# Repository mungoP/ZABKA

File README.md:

# ŻABKA

**Zero-moment Assisted Bipedal Kinetic Android**

By Mungo Prus-Shearer and Adam Chrostowski

ŻABKA ("little frog" in Polish) is a DIY 3D-printed bipedal robot with custom FOC motor controllers on every joint. The current focus is the legs.

<p align="center"><em>Left: leg assembly (Onshape). Right: motor controller board (KiCad).</em></p>

## Specs (planned)

|                      |                                                                                                |
| -------------------- | ---------------------------------------------------------------------------------------------- |
| **Height**           | 0.45m (without upper body) 0.85m (full body)                                                   |
| **Legs**             | 5 DoF each (3 hip, 1 knee, 1 ankle), 10 DoF total                                              |
| **Actuators**        | MAD 5008 170KV BLDC motors, each with a custom STSPIN32G4 FOC controller board, on one CAN bus |
| **Compute**          | Raspberry Pi 4 running the walking policy, ESP32-C3 as the real-time CAN bridge                |
| **Power**            | 12S LiPo, two 6S 4000 mAh packs soldered in series (36–50.4 V)                                 |
| **Structure**        | 3D-printed PETG, 4 walls, 10–20 % infill                                                       |
| **Estimated weight** | ~8 kg without arms                                                                             |

## System overview

```mermaid
flowchart LR
    PI["Raspberry Pi 4<br/>RL policy"] <-- "USB serial" --> ESP["ESP32-C3<br/>CAN bridge"]
    IMU["IMU"] --> ESP
    ESP <-- "CAN 1 Mbps" --> J["10 × motor + FOC board<br/>(5 per leg)"]
    BAT["12S LiPo + BMS"] -- "36–50.4 V" --> J
    BAT -- "5 V buck" --> PI
```

The Pi runs the walking policy at 50 Hz. The ESP32 exchanges commands and joint state with all 10 motor boards over CAN at 200 Hz, and each board closes its own FOC current loop and PD position loop. See [`docs/system_architecture.md`](docs/system_architecture.md) for the full design.

## Repository map

| Path                     | Contents                                                                  |
| ------------------------ | ------------------------------------------------------------------------- |
| [`BOM.csv`](BOM.csv)     | Combined bill of materials with running total                             |
| [`docs/`](docs/)         | System architecture, CAN protocol, per-category BOMs, datasheets          |
| [`cad/`](cad/)           | Onshape link and STEP exports of the printed parts                        |
| [`pcb/`](pcb/)           | KiCad project and JLCPCB fabrication files for the motor controller board |
| [`lib/`](lib/)           | Custom KiCad symbols, footprints and 3D models                            |
| [`firmware/`](firmware/) | Motor board FOC firmware and ESP32 CAN bridge firmware                    |
| [`software/`](software/) | Simulation, policy training and the code that runs on the Pi              |

## Status

| Subsystem                     | Status                                                                   |
| ----------------------------- | ------------------------------------------------------------------------ |
| Mechanical design             | Done ([Onshape](cad/))                                                   |
| 3D printing                   | In progress                                                              |
| Motor controller board        | Ordered from JLCPCB, shipping                                            |
| Motors, bearings, fasteners   | In hand                                                                  |
| Control and power electronics | Being purchased ([`electronics_BOM.csv`](docs/BOMs/electronics_BOM.csv)) |
| Firmware                      | Planned                                                                  |
| Walking policy                | Planned                                                                  |

## License

ŻABKA is open source:

- **Hardware** (`pcb/`, `lib/`, `cad/`): [CERN-OHL-S-2.0](LICENSES/CERN-OHL-S-2.0.txt)
- **Firmware and software** (`firmware/`, `software/`): [GPL-3.0-or-later](LICENSES/GPL-3.0.txt)
- **Documentation** (`docs/`, READMEs, BOMs): [CC BY-SA 4.0](LICENSES/CC-BY-SA-4.0.txt)

Anyone may use, modify, build and sell the designs, as long as modified versions are released under the same licence. See [`LICENSE`](LICENSE) for details.

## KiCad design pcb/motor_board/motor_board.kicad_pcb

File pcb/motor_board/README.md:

# Motor Board Planned Components

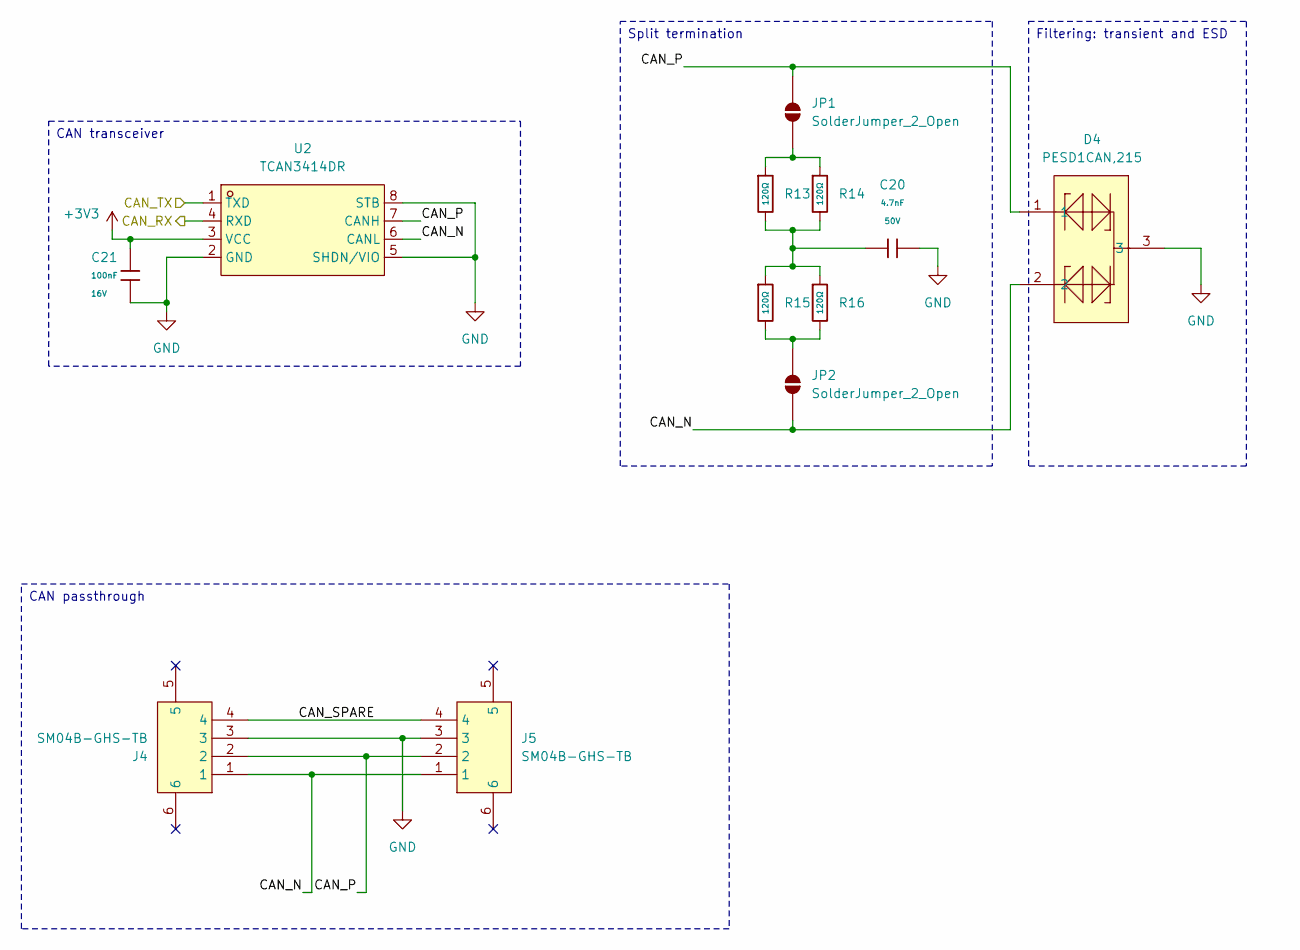
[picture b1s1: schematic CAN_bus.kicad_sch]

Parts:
C20: 4.7nF; C_0402; Voltage Rated 50V; Tolerance ±10%; Part 0402B472K500NT; LCSC C1538
C21: 100nF; C_0402; Voltage Rated 16V; Tolerance ±10%; Part CL05B104KO5NNNC; LCSC C1525
D4: PESD1CAN,215; SOT-23_L2.9-W1.3-P1.90-LS2.4-BR; MPN PESD1CAN,215; LCSC Part C15771
J4, J5: SM04B-GHS-TB; CONN-SMD_4P-P1.25_SM04B-GHS-TB-LF-SN; MPN SM04B-GHS-TB(LF)(SN); LCSC Part C189895
JP1, JP2: SolderJumper_2_Open; SolderJumper-2_P1.3mm_Open_Pad1.0x1.5mm
R13, R14, R15, R16: 120Ω; R_0402; Overload Voltage (Max) 50V; Tolerance ±1%; Part 0402WGF1200TCE; LCSC C25079
U2: TCAN3414DR; SOIC-8_L4.9-W3.9-P1.27-LS6.0-BL; MPN TCAN3414DR; LCSC Part C22396693

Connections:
+3V3: C21.1, U2.3 (VCC); also elsewhere on the board
/CAN bus/CAN_N: D4.2, J4.1, J5.1, JP2.1 (A), U2.6 (CANL)
/CAN bus/CAN_P: D4.1, J4.2, J5.2, JP1.2 (B), U2.7 (CANH)
/CAN bus/CAN_RX: U2.4 (RXD); also elsewhere on the board
/CAN bus/CAN_SPARE: J4.4, J5.4
/CAN bus/CAN_TX: U2.1 (TXD); also elsewhere on the board
GND: C20.2, C21.2, D4.3, J4.3, J5.3, U2.2 (GND), U2.5 (SHDN/VIO), U2.8 (STB); also elsewhere on the board
unnamed: C20.1, R13.2, R14.2, R15.1, R16.1
unnamed: JP1.1 (A), R13.1, R14.1
unnamed: JP2.2 (B), R15.2, R16.2

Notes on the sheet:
Split termination
CAN transceiver
CAN passthrough
Filtering: transient and ESD

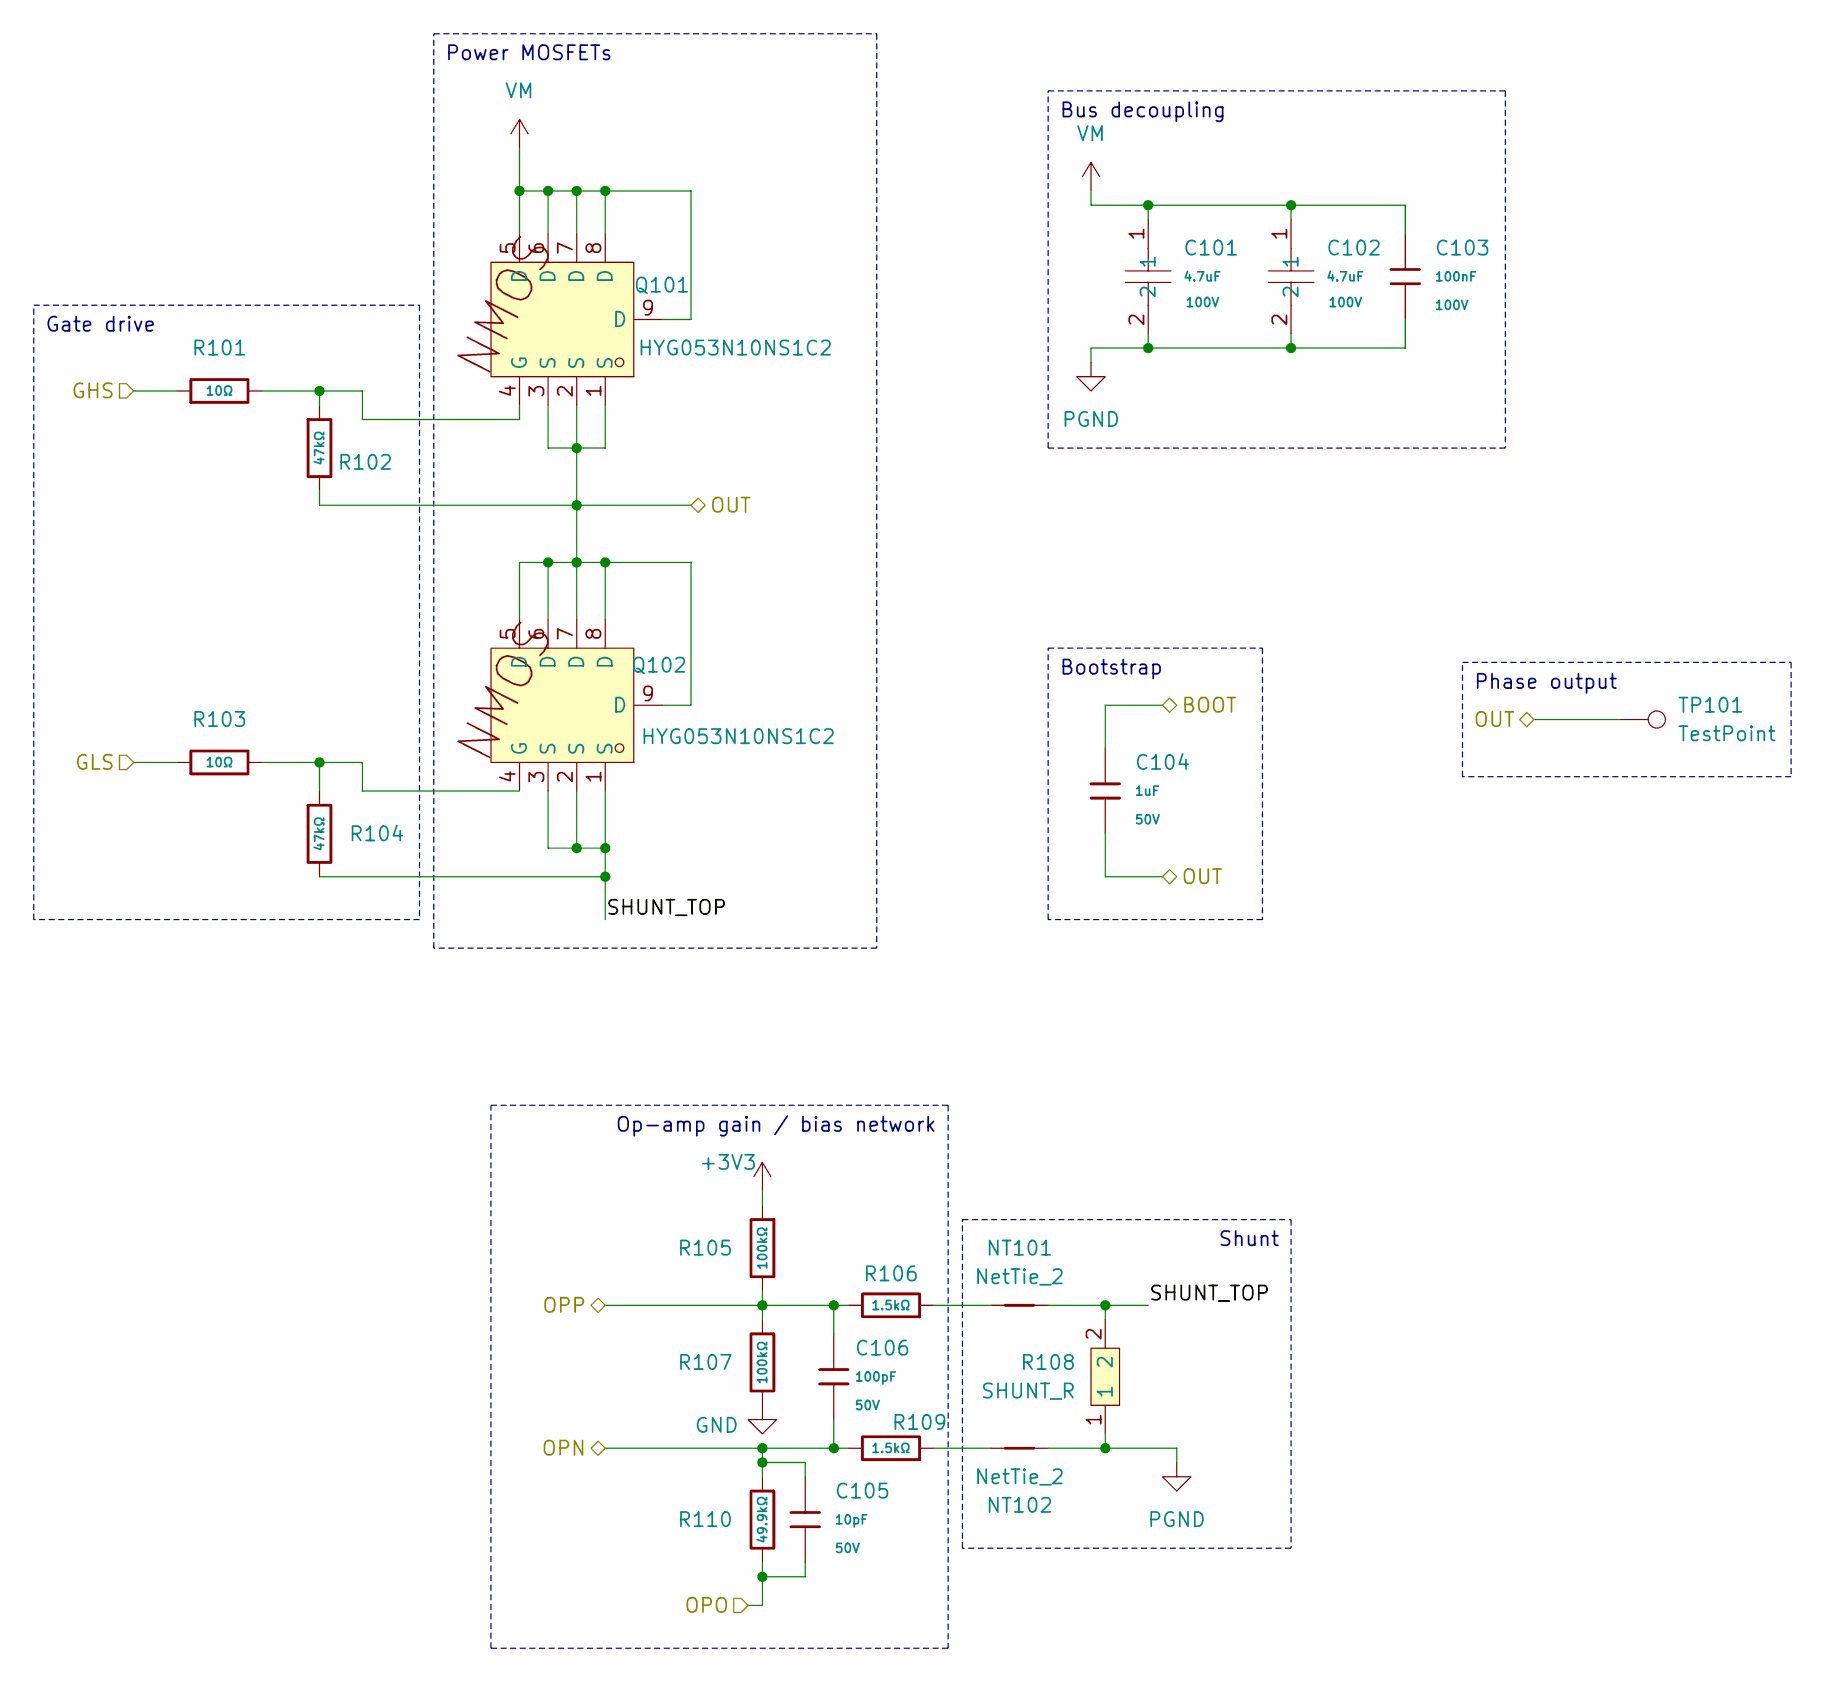
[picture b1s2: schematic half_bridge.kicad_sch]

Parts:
C101, C102: 4.7uF; C1210_no-silk; MPN C1210X475K101T; LCSC Part C337978
C103: 100nF; C_0805; Voltage Rated 100V; Tolerance ±10%; Part CL21B104KCFNNNE; LCSC C28233
C104: 1uF; C_0603; Voltage Rated 50V; Tolerance ±10%; Part CL10A105KB8NNNC; LCSC C15849
C105: 10pF; C_0402; Voltage Rated 50V; Tolerance ±5%; Part CL05C100JB5NNNC; LCSC C32949
C106: 100pF; C_0402; Voltage Rated 50V; Tolerance ±5%; Part 0402CG101J500NT; LCSC C1546
NT101, NT102: NetTie_2; NetTie-2_SMD_Pad0.5mm
Q101, Q102: HYG053N10NS1C2; PDFN-8_L5.8-W5.0-P1.27-LS6.2-BL; MPN HYG053N10NS1C2; LCSC Part C2986239
R101, R103: 10Ω; R_0402; Overload Voltage (Max) 50V; Tolerance ±1%; Part 0402WGF100JTCE; LCSC C25077
R102, R104: 47kΩ; R_0402; Overload Voltage (Max) 50V; Tolerance ±1%; Part 0402WGF4702TCE; LCSC C25792
R105, R107: 100kΩ; R_0603; Overload Voltage (Max) 75V; Tolerance ±1%; Part 0603WAF1003T5E; LCSC C25803
R106, R109: 1.5kΩ; R_0603; Overload Voltage (Max) 75V; Tolerance ±1%; Part 0603WAF1501T5E; LCSC C22843
R108: SHUNT_R; RES-SMD_L6.4-W3.2_LR2512D-3W-1MR; MPN LR2512D-3W-1mR-1%; LCSC Part C500734
R110: 49.9kΩ; R_0402; Overload Voltage (Max) 50V; Tolerance ±1%; Part 0402WGF4992TCE; LCSC C25897
TP101: TestPoint; TestPoint_Pad_4.0x4.0mm

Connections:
+3V3: R105.1; also elsewhere on the board
/Controller/BOOT1: C104.1; also elsewhere on the board
/Controller/GHS1: R101.1; also elsewhere on the board
/Controller/GLS1: R103.1; also elsewhere on the board
/Controller/OPN1: C105.1, C106.2, R109.2, R110.1; also elsewhere on the board
/Controller/OPO1: C105.2, R110.2; also elsewhere on the board
/Controller/OPP1: C106.1, R105.2, R106.2, R107.1; also elsewhere on the board
/Controller/OUT1: C104.2, Q101.1 (S), Q101.2 (S), Q101.3 (S), Q102.5 (D), Q102.6 (D), Q102.7 (D), Q102.8 (D), Q102.9 (D), R102.2, TP101.1 (1_1); also elsewhere on the board
/Half bridge - U/SHUNT_TOP: NT101.1, Q102.1 (S), Q102.2 (S), Q102.3 (S), R104.2, R108.2
GND: R107.2; also elsewhere on the board
unnamed: NT101.2, R106.1
unnamed: NT102.1, R109.1
unnamed: Q101.4 (G), R101.2, R102.1
unnamed: Q102.4 (G), R103.2, R104.1
PGND: C101.2, C102.2, C103.2, NT102.2, R108.1; also elsewhere on the board
VM: C101.1, C102.1, C103.1, Q101.5 (D), Q101.6 (D), Q101.7 (D), Q101.8 (D), Q101.9 (D); also elsewhere on the board

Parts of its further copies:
C201, C202, C301, C302: 4.7uF; C1210_no-silk; MPN C1210X475K101T; LCSC Part C337978
C203, C303: 100nF; C_0805; Voltage Rated 100V; Tolerance ±10%; Part CL21B104KCFNNNE; LCSC C28233
C204, C304: 1uF; C_0603; Voltage Rated 50V; Tolerance ±10%; Part CL10A105KB8NNNC; LCSC C15849
C205, C305: 10pF; C_0402; Voltage Rated 50V; Tolerance ±5%; Part CL05C100JB5NNNC; LCSC C32949
C206, C306: 100pF; C_0402; Voltage Rated 50V; Tolerance ±5%; Part 0402CG101J500NT; LCSC C1546
NT201, NT202, NT301, NT302: NetTie_2; NetTie-2_SMD_Pad0.5mm
Q201, Q202, Q301, Q302: HYG053N10NS1C2; PDFN-8_L5.8-W5.0-P1.27-LS6.2-BL; MPN HYG053N10NS1C2; LCSC Part C2986239
R201, R203, R301, R303: 10Ω; R_0402; Overload Voltage (Max) 50V; Tolerance ±1%; Part 0402WGF100JTCE; LCSC C25077
R202, R204, R302, R304: 47kΩ; R_0402; Overload Voltage (Max) 50V; Tolerance ±1%; Part 0402WGF4702TCE; LCSC C25792
R205, R207, R305, R307: 100kΩ; R_0603; Overload Voltage (Max) 75V; Tolerance ±1%; Part 0603WAF1003T5E; LCSC C25803
R206, R209, R306, R309: 1.5kΩ; R_0603; Overload Voltage (Max) 75V; Tolerance ±1%; Part 0603WAF1501T5E; LCSC C22843
R208, R308: SHUNT_R; RES-SMD_L6.4-W3.2_LR2512D-3W-1MR; MPN LR2512D-3W-1mR-1%; LCSC Part C500734
R210, R310: 49.9kΩ; R_0402; Overload Voltage (Max) 50V; Tolerance ±1%; Part 0402WGF4992TCE; LCSC C25897
TP201, TP301: TestPoint; TestPoint_Pad_4.0x4.0mm

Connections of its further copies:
+3V3: R205.1, R305.1; also elsewhere on the board
/Controller/BOOT2: C204.1; also elsewhere on the board
/Controller/BOOT3: C304.1; also elsewhere on the board
/Controller/GHS2: R201.1; also elsewhere on the board
/Controller/GHS3: R301.1; also elsewhere on the board
/Controller/GLS2: R203.1; also elsewhere on the board
/Controller/GLS3: R303.1; also elsewhere on the board
/Controller/OPN2: C205.1, C206.2, R209.2, R210.1; also elsewhere on the board
/Controller/OPN3: C305.1, C306.2, R309.2, R310.1; also elsewhere on the board
/Controller/OPO2: C205.2, R210.2; also elsewhere on the board
/Controller/OPO3: C305.2, R310.2; also elsewhere on the board
/Controller/OPP2: C206.1, R205.2, R206.2, R207.1; also elsewhere on the board
/Controller/OPP3: C306.1, R305.2, R306.2, R307.1; also elsewhere on the board
/Controller/OUT2: C204.2, Q201.1 (S), Q201.2 (S), Q201.3 (S), Q202.5 (D), Q202.6 (D), Q202.7 (D), Q202.8 (D), Q202.9 (D), R202.2, TP201.1 (1_1); also elsewhere on the board
/Controller/OUT3: C304.2, Q301.1 (S), Q301.2 (S), Q301.3 (S), Q302.5 (D), Q302.6 (D), Q302.7 (D), Q302.8 (D), Q302.9 (D), R302.2, TP301.1 (1_1); also elsewhere on the board
/Half bridge - V/SHUNT_TOP: NT201.1, Q202.1 (S), Q202.2 (S), Q202.3 (S), R204.2, R208.2
/Half bridge - W/SHUNT_TOP: NT301.1, Q302.1 (S), Q302.2 (S), Q302.3 (S), R304.2, R308.2
GND: R207.2, R307.2; also elsewhere on the board
unnamed: NT201.2, R206.1
unnamed: NT202.1, R209.1
unnamed: NT301.2, R306.1
unnamed: NT302.1, R309.1
unnamed: Q201.4 (G), R201.2, R202.1
unnamed: Q202.4 (G), R203.2, R204.1
unnamed: Q301.4 (G), R301.2, R302.1
unnamed: Q302.4 (G), R303.2, R304.1
PGND: C201.2, C202.2, C203.2, C301.2, C302.2, C303.2, NT202.2, NT302.2, R208.1, R308.1; also elsewhere on the board
VM: C201.1, C202.1, C203.1, C301.1, C302.1, C303.1, Q201.5 (D), Q201.6 (D), Q201.7 (D), Q201.8 (D), Q201.9 (D), Q301.5 (D), Q301.6 (D), Q301.7 (D), Q301.8 (D), Q301.9 (D); also elsewhere on the board

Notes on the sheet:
Bootstrap
Gate drive
Shunt
Bus decoupling
Power MOSFETs
Op-amp gain / bias network
Phase output

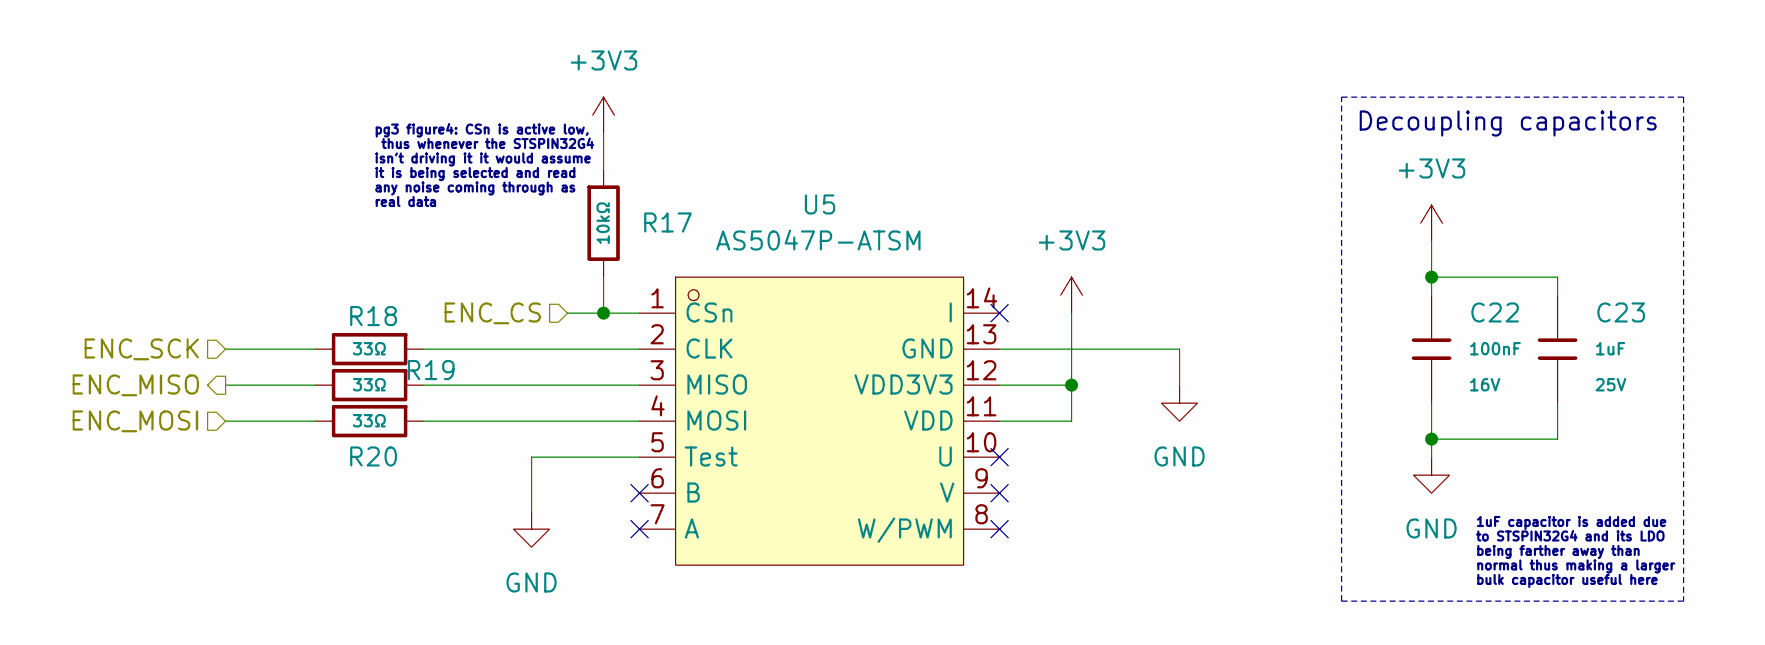
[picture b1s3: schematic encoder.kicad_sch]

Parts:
C22: 100nF; C_0402; Voltage Rated 16V; Tolerance ±10%; Part CL05B104KO5NNNC; LCSC C1525
C23: 1uF; C_0402; Voltage Rated 25V; Tolerance ±10%; Part CL05A105KA5NQNC; LCSC C52923
R17: 10kΩ; R_0402; Overload Voltage (Max) 50V; Tolerance ±1%; Part 0402WGF1002TCE; LCSC C25744
R18, R19, R20: 33Ω; R_0402; Overload Voltage (Max) 50V; Tolerance ±1%; Part 0402WGF330JTCE; LCSC C25105
U5: AS5047P-ATSM; TSSOP-14_L5.0-W4.4-P0.65-LS6.4-BL; MPN AS5047P-ATSM; LCSC Part C962063

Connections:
+3V3: C22.1, C23.1, R17.1, U5.11 (VDD), U5.12 (VDD3V3); also elsewhere on the board
/Controller/ENC_CS: R17.2, U5.1 (CSn); also elsewhere on the board
/Controller/ENC_MISO: R19.2; also elsewhere on the board
/Controller/ENC_MOSI: R20.2; also elsewhere on the board
/Controller/ENC_SCK: R18.2; also elsewhere on the board
GND: C22.2, C23.2, U5.5 (Test), U5.13 (GND); also elsewhere on the board
unnamed: R18.1, U5.2 (CLK)
unnamed: R19.1, U5.3 (MISO)
unnamed: R20.1, U5.4 (MOSI)

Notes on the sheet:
pg3 figure4: CSn is active low, thus whenever the STSPIN32G4 isn't driving it it would assume it is being selected and read any noise coming through as real data
1uF capacitor is added due to STSPIN32G4 and its LDO being farther away than normal thus making a larger bulk capacitor useful here
Decoupling capacitors

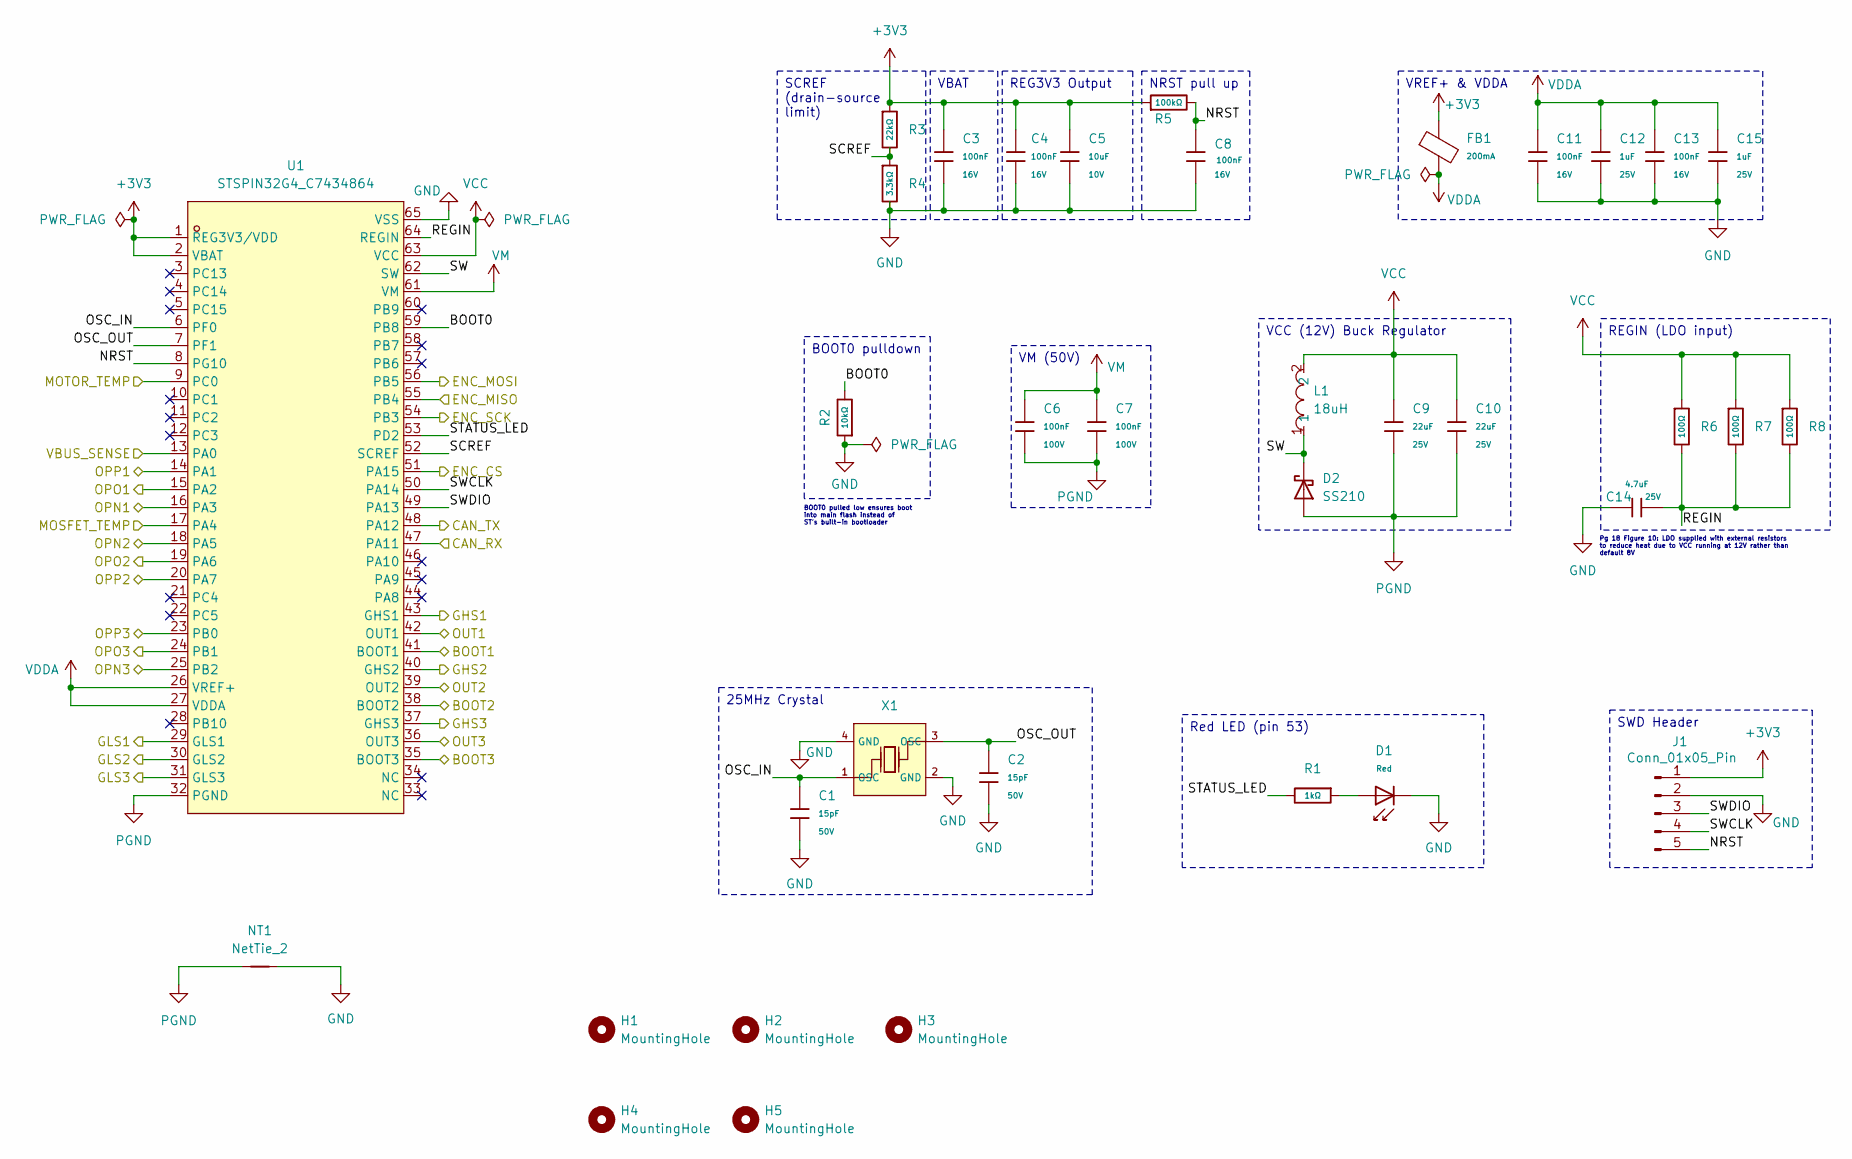
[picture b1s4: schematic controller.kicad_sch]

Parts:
C1, C2: 15pF; C_0402; Voltage Rated 50V; Tolerance ±5%; Part 0402CG150J500NT; LCSC C1548
C3, C4, C8, C11, C13: 100nF; C_0402; Voltage Rated 16V; Tolerance ±10%; Part CL05B104KO5NNNC; LCSC C1525
C5: 10uF; C_0603; Voltage Rated 10V; Tolerance ±10%; Part CL10A106KP8NNNC; LCSC C19702
C6, C7: 100nF; C_0805; Voltage Rated 100V; Tolerance ±10%; Part CL21B104KCFNNNE; LCSC C28233
C9, C10: 22uF; C_1206; Voltage Rated 25V; Tolerance ±10%; Part CL31A226KAHNNNE; LCSC C12891
C12, C15: 1uF; C_0402; Voltage Rated 25V; Tolerance ±10%; Part CL05A105KA5NQNC; LCSC C52923
C14: 4.7uF; C_0805; Voltage Rated 25V; Tolerance ±10%; Part CL21A475KAQNNNE; LCSC C1779
D1: Red; D_0603; Part KT-0603R; LCSC C2286
D2: SS210; D_SMA; Forward Voltage (Vf@If) 850mV@2A; Reverse Voltage (Vr) 100V; Part SS210; LCSC C14996
FB1: FB_0603; Current Rating 200mA; Tolerance ±25%; Part GZ1608D601TF; LCSC C1002
H1, H2, H3, H4, H5: MountingHole; MountingHole_4.3mm_M4
J1: Conn_01x05_Pin; JST_GH_SM05B-GHS-TB_1x05-1MP_P1.25mm_Horizontal
L1: 18uH; IND-SMD_L6.0-W6.0_FNR60XXS; MPN FNR6020S180MT; LCSC Part C168016
NT1: NetTie_2; NetTie-2_SMD_Pad0.5mm
R1: 1kΩ; R_0402; Overload Voltage (Max) 50V; Tolerance ±1%; Part 0402WGF1001TCE; LCSC C11702
R2: 10kΩ; R_0402; Overload Voltage (Max) 50V; Tolerance ±1%; Part 0402WGF1002TCE; LCSC C25744
R3: 22kΩ; R_0402; Overload Voltage (Max) 50V; Tolerance ±1%; Part 0402WGF2202TCE; LCSC C25768
R4: 3.3kΩ; R_0402; Overload Voltage (Max) 50V; Tolerance ±1%; Part 0402WGF3301TCE; LCSC C25890
R5: 100kΩ; R_0402; Overload Voltage (Max) 50V; Tolerance ±1%; Part 0402WGF1003TCE; LCSC C25741
R6, R7, R8: 100Ω; R_1206; Overload Voltage (Max) 200V; Tolerance ±1%; Part 1206W4F1000T5E; LCSC C17901
U1: STSPIN32G4_C7434864; VFQFPN-64_L9.0-W9.0-P0.50-TL-EP4.0; MPN STSPIN32G4; LCSC Part C7434864
X1: X322525MOB4SI; OSC-SMD_4P-L3.2-W2.5-BL; Frequency Tolerance ±10ppm; Part X322525MOB4SI; LCSC C9006

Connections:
+3V3: C3.1, C4.1, C5.1, FB1.1, J1.1, R3.1, R5.1, U1.1 (REG3V3/VDD), U1.2 (VBAT); also elsewhere on the board
/CAN bus/CAN_RX: U1.47 (PA11); also elsewhere on the board
/CAN bus/CAN_TX: U1.48 (PA12); also elsewhere on the board
/Controller/BOOT0: R2.2, U1.59 (PB8)
/Controller/BOOT1: U1.41 (BOOT1); also elsewhere on the board
/Controller/BOOT2: U1.38 (BOOT2); also elsewhere on the board
/Controller/BOOT3: U1.35 (BOOT3); also elsewhere on the board
/Controller/ENC_CS: U1.51 (PA15); also elsewhere on the board
/Controller/ENC_MISO: U1.55 (PB4); also elsewhere on the board
/Controller/ENC_MOSI: U1.56 (PB5); also elsewhere on the board
/Controller/ENC_SCK: U1.54 (PB3); also elsewhere on the board
/Controller/GHS1: U1.43 (GHS1); also elsewhere on the board
/Controller/GHS2: U1.40 (GHS2); also elsewhere on the board
/Controller/GHS3: U1.37 (GHS3); also elsewhere on the board
/Controller/GLS1: U1.29 (GLS1); also elsewhere on the board
/Controller/GLS2: U1.30 (GLS2); also elsewhere on the board
/Controller/GLS3: U1.31 (GLS3); also elsewhere on the board
/Controller/MOSFET_TEMP: U1.17 (PA4); also elsewhere on the board
/Controller/MOTOR_TEMP: U1.9 (PC0); also elsewhere on the board
/Controller/NRST: C8.1, J1.5, R5.2, U1.8 (PG10)
/Controller/OPN1: U1.16 (PA3); also elsewhere on the board
/Controller/OPN2: U1.18 (PA5); also elsewhere on the board
/Controller/OPN3: U1.25 (PB2); also elsewhere on the board
/Controller/OPO1: U1.15 (PA2); also elsewhere on the board
/Controller/OPO2: U1.19 (PA6); also elsewhere on the board
/Controller/OPO3: U1.24 (PB1); also elsewhere on the board
/Controller/OPP1: U1.14 (PA1); also elsewhere on the board
/Controller/OPP2: U1.20 (PA7); also elsewhere on the board
/Controller/OPP3: U1.23 (PB0); also elsewhere on the board
/Controller/OSC_IN: C1.1, U1.6 (PF0), X1.1 (OSC)
/Controller/OSC_OUT: C2.1, U1.7 (PF1), X1.3 (OSC)
/Controller/OUT1: U1.42 (OUT1); also elsewhere on the board
/Controller/OUT2: U1.39 (OUT2); also elsewhere on the board
/Controller/OUT3: U1.36 (OUT3); also elsewhere on the board
/Controller/REGIN: C14.2, R6.2, R7.2, R8.2, U1.64 (REGIN)
/Controller/SCREF: R3.2, R4.1, U1.52 (SCREF)
/Controller/STATUS_LED: R1.2, U1.53 (PD2)
/Controller/SW: D2.1, L1.1, U1.62 (SW)
/Controller/SWCLK: J1.4, U1.50 (PA14)
/Controller/SWDIO: J1.3, U1.49 (PA13)
/Controller/VBUS_SENSE: U1.13 (PA0); also elsewhere on the board
GND: C1.2, C2.2, C3.2, C4.2, C5.2, C8.2, C11.2, C12.2, C13.2, C14.1, C15.2, D1.1, J1.2, NT1.2, R2.1, R4.2, U1.65 (VSS), X1.2 (GND), X1.4 (GND); also elsewhere on the board
unnamed: D1.2, R1.1
PGND: C6.2, C7.2, C9.2, C10.2, D2.2, NT1.1, U1.32 (PGND); also elsewhere on the board
VCC: C9.1, C10.1, L1.2, R6.1, R7.1, R8.1, U1.63 (VCC)
VDDA: C11.1, C12.1, C13.1, C15.1, FB1.2, U1.26 (VREF+), U1.27 (VDDA)
VM: C6.1, C7.1, U1.61 (VM); also elsewhere on the board

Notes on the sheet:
Pg 18 Figure 10: LDO supplied with external resistors to reduce heat due to VCC running at 12V rather than default 8V
BOOT0 pulled low ensures boot into main flash instead of ST's built-in bootloader
Red LED (pin 53)
BOOT0 pulldown
SCREF (drain-source limit)
25MHz Crystal
NRST pull up
REG3V3 Output
VM (50V)
VCC (12V) Buck Regulator
VREF+ & VDDA
SWD Header
VBAT
REGIN (LDO input)

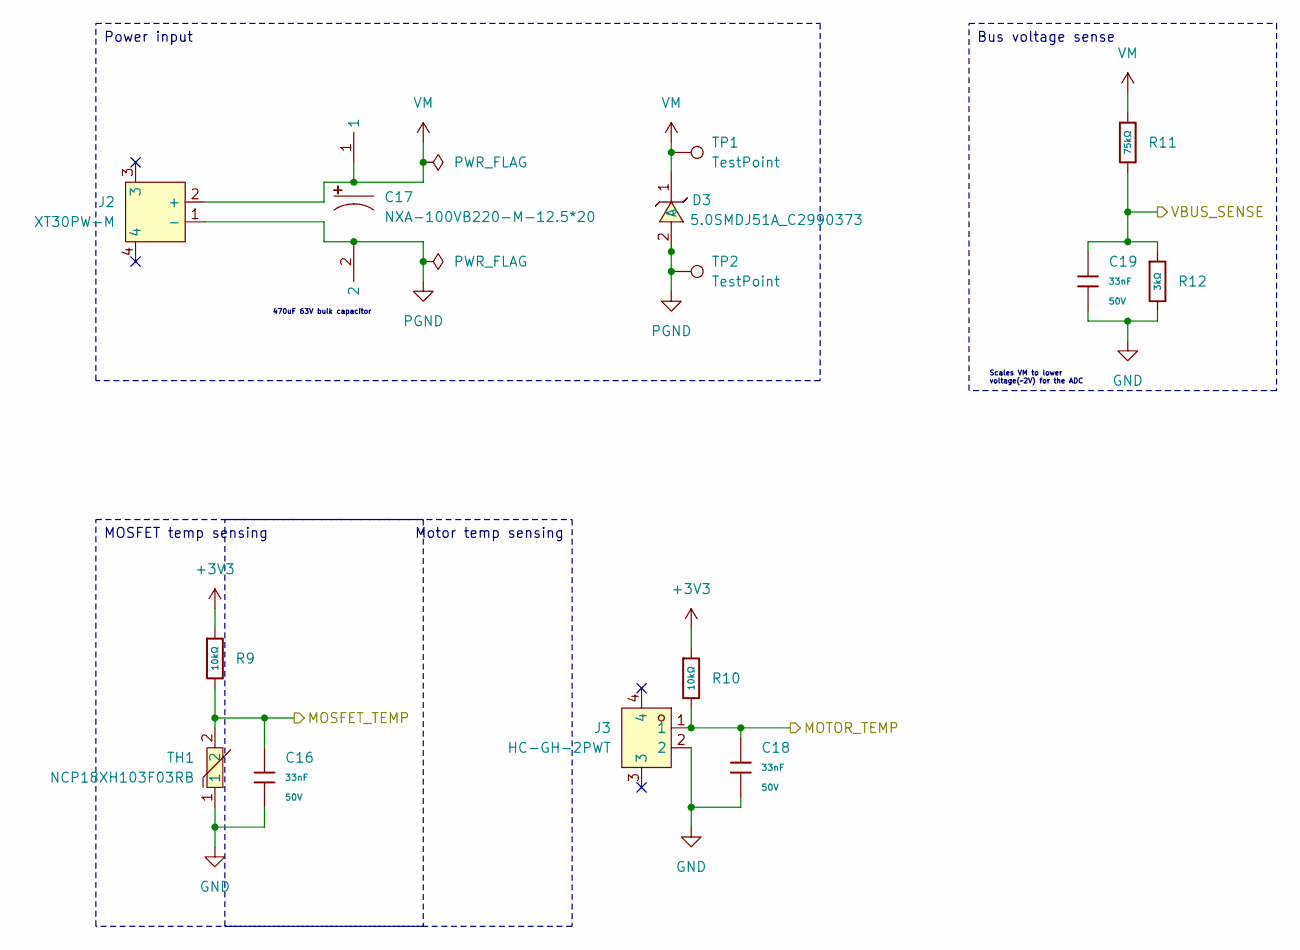
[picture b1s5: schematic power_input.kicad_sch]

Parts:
C16, C18, C19: 33nF; C_0603; Voltage Rated 50V; Tolerance ±10%; Part CL10B333KB8NNNC; LCSC C21117
C17: NXA-100VB220-M-12.5*20; CAP-TH_BD12.5-P5.00-D0.6-FD; MPN NXA 100V220 M 12.5*20; LCSC Part C350119
D3: 5.0SMDJ51A_C2990373; SMC_L6.9-W5.9-LS7.9-RD; MPN 5.0SMDJ51A; LCSC Part C2990373
J2: XT30PW-M; CONN-TH_XT30PW-M; MPN XT30PW-M30.G.Y; LCSC Part C431092
J3: HC-GH-2PWT; CONN-SMD_2P-P1.25_HCTL_HC-GH-2PWT; MPN HC-GH-2PWT; LCSC Part C2845397
R9, R10: 10kΩ; R_0402; Overload Voltage (Max) 50V; Tolerance ±1%; Part 0402WGF1002TCE; LCSC C25744
R11: 75kΩ; R_0603; Overload Voltage (Max) 75V; Tolerance ±1%; Part 0603WAF7502T5E; LCSC C23242
R12: 3kΩ; R_0603; Overload Voltage (Max) 75V; Tolerance ±1%; Part 0603WAF3001T5E; LCSC C4211
TH1: NCP18XH103F03RB; R0603; MPN NCP18XH103F03RB; LCSC Part C13564
TP1, TP2: TestPoint; TestPoint_Pad_1.5x1.5mm

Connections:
+3V3: R9.1, R10.1; also elsewhere on the board
/Controller/MOSFET_TEMP: C16.1, R9.2, TH1.2; also elsewhere on the board
/Controller/MOTOR_TEMP: C18.1, J3.1, R10.2; also elsewhere on the board
/Controller/VBUS_SENSE: C19.1, R11.2, R12.1; also elsewhere on the board
GND: C16.2, C18.2, C19.2, J3.2, R12.2, TH1.1; also elsewhere on the board
PGND: C17.2, D3.2 (A), J2.1 (-), TP2.1 (1_1); also elsewhere on the board
VM: C17.1, D3.1 (C), J2.2 (+), R11.1, TP1.1 (1_1); also elsewhere on the board

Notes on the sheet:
470uF 63V bulk capacitor
Scales VM to lower voltage(~2V) for the ADC
Motor temp sensing
MOSFET temp sensing
Bus voltage sense
Power input
